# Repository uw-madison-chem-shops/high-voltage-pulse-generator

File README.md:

# High Voltage Pulse Generator 

Our adaptation of work by Nathan M. Hoffman:

>[Note: An inexpensive square waveform ion funnel driver](http://dx.doi.org/10.1063/1.4974345); Nathan M Hoffman, Bojana Bojana Opačić, and Peter T.A. Reilly; Review of Scientific Instruments, 88, 016104 (2017) 

## PCB

This PCB was designed using KiCAD version 6.
Refer to `HV-pulse-generator.pdf` for schematic.
PCB images generated with [tracespace](https://github.com/tracespace/tracespace) follow.

## Changelog

### Unprinted

### C

#### Added
- link to this repository

### B

#### Added
- initial design

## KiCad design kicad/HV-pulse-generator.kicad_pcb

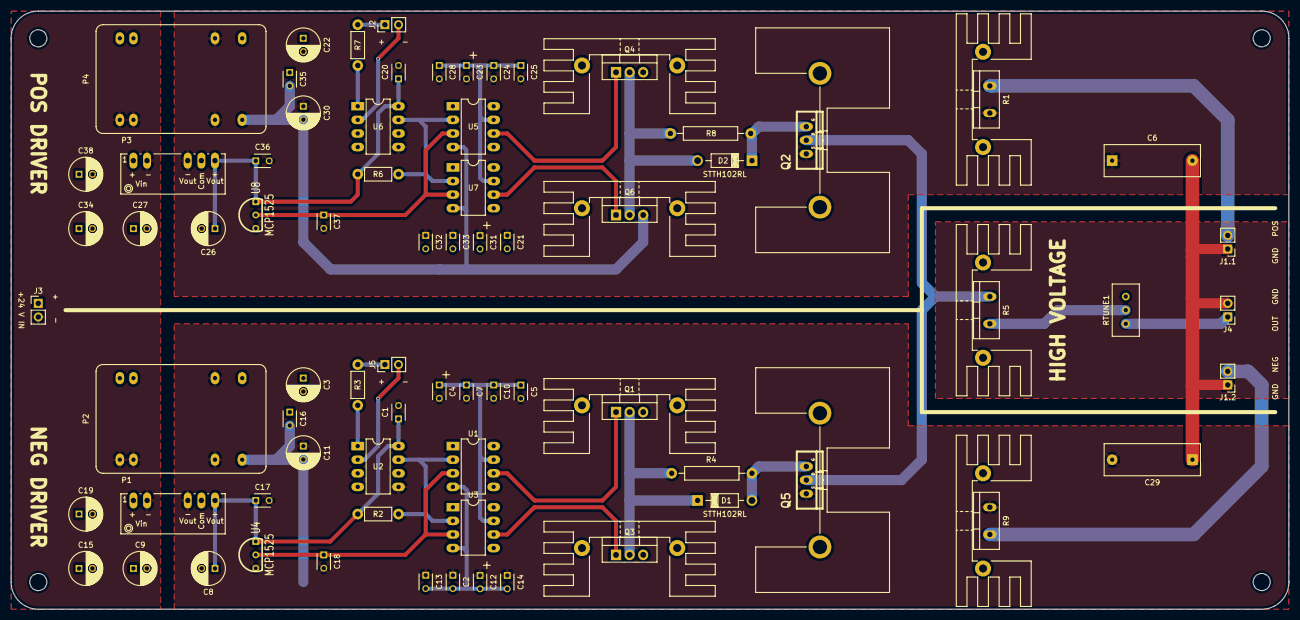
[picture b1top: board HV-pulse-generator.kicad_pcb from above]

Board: 2 copper layers, 238.8 x 111.8 mm, 74 parts (0 on the bottom side), 34 nets.

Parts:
C1, C17, C20, C36: 0.1uF; C_Disc_D3_P2.5
C2, C7, C10, C14, C16, C21, C25, C28, C33, C35: 0.01uF; C_Disc_D3_P2.5
C3, C8, C9, C11, C15, C19, C22, C26, C27, C30, C34, C38: 100uF; C_Radial_D6.3_L11.2_P2.5
C4, C12, C23, C31: 2.2uF; C_Tantalum_D3_P2.5
C5, C13, C24, C32: 1uF; C_Disc_D3_P2.5
C6, C29: 0.22uF; ECW-FA2J(10-68)4J
C18, C37: 10uF; C_Disc_D3_P2.5
D1, D2: STTH102RL; Diode_DO-41_SOD81_Horizontal_RM10
J1.1, J1.2, J3: Pin1=24V Pin2=GND; PinHeader_1x02_P2.54mm_Vertical
J2, J5: Pin1=TTL Pin2=GND; PinHeader_1x02_P2.54mm_Vertical
J4: CONN_01X02; PinHeader_1x02_P2.54mm_Vertical
P1, P3: PEM2-S24-S5-S; DCDC-Conv_CUI_PEM2_DUAL
P2, P4: JCJ0824D15
Q1, Q4: IRF9610PBF; TO-220-3_Vertical
Q2: FQP3P50; FQP3P20
Q3, Q6: IRF710PBF; TO-220-3_Vertical
Q5: FQP13N50; FQP4N20L
R1, R9: 50; Resistor_TO-220_Vertical
R2, R3, R6, R7: 365; Resistor_Horizontal_RM7mm
R4, R8: 5.1; Resistor_Horizontal_RM15mm
R5: 100; Resistor_TO-220_Vertical
RTUNE1: 200; Potentiometer_Bourns_3296W_Vertical
U1, U3, U5, U7: LM7171; DIP-8_W7.62mm_LongPads
U2, U6: ICPL2631; DIP-8_W7.62mm_LongPads
U4, U8: MCP1525; TO92-MCP1525

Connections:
+24V: C9.1, C15.1, C19.1, C27.1, C34.1, C38.1, J3.1, P1.1, P2.22, P2.23, P3.1, P4.22, P4.23
+VDC: J1.1.2, R1.2
-VDC: J1.2.2, R9.1
/Sheet5F8C1FCD/+2P5V: C18.1, U1.3, U3.3, U4.2
/Sheet5F8C1FCD/+5V: C1.1, C8.1, C17.1, P1.7, R2.2, U2.8, U4.1
/Sheet5F8C1FCD/+15V: C3.1, C4.1, C5.1, C7.1, C10.1, C16.1, P2.14, Q1.3, U1.7, U3.7
/Sheet5F8C1FCD/-15V: C2.2, C11.2, C12.2, C13.2, C14.2, C16.2, P2.11, Q3.3, U1.4, U3.4
/Sheet5F8C1FCD/COM: C1.2, C2.1, C3.2, C4.2, C5.2, C7.2, C8.2, C10.2, C11.1, C12.1, C13.1, C14.1, C17.2, C18.2, C29.2, P1.5, P2.9, P2.16, Q5.1, R9.2, U2.5, U4.3
/Sheet5F8C1FCD/GATE: D1.1, Q1.2, Q3.2, R4.2
/Sheet5F8C1FCD/TTL+: J5.1, R3.2
/Sheet5F8C1FCD/TTL-: J5.2, U2.2
/sheet5F874D32/+2P5V: C37.1, U5.3, U7.3, U8.2
/sheet5F874D32/+5V: C20.1, C26.1, C36.1, P3.7, R6.2, U6.8, U8.1
/sheet5F874D32/+15V: C22.1, C23.1, C24.1, C25.1, C28.1, C35.1, P4.14, Q4.3, U5.7, U7.7
/sheet5F874D32/-15V: C21.2, C30.2, C31.2, C32.2, C33.2, C35.2, P4.11, Q6.3, U5.4, U7.4
/sheet5F874D32/COM: C6.1, C20.2, C21.1, C22.2, C23.2, C24.2, C25.2, C26.2, C28.2, C30.1, C31.1, C32.1, C33.1, C36.2, C37.2, P3.5, P4.9, P4.16, Q2.1, R1.1, U6.5, U8.3
/sheet5F874D32/GATE: D2.2, Q4.2, Q6.2, R8.1
/sheet5F874D32/TTL+: J2.1, R7.2
/sheet5F874D32/TTL-: J2.2, U6.2
GND: C6.2, C29.1, J1.1.1, J1.2.1, J4.2
GNDPWR: C9.2, C15.2, C19.2, C27.2, C34.2, C38.2, J3.2, P1.2, P2.2, P2.3, P3.2, P4.2, P4.3
unnamed: D1.2, Q5.3, R4.1
unnamed: D2.1, Q2.3, R8.2
unnamed: J4.1, RTUNE1.3
unnamed: Q1.1, U1.6
unnamed: Q2.2, Q5.2, R5.2
unnamed: Q3.1, U3.6
unnamed: Q4.1, U5.6
unnamed: Q6.1, U7.6
unnamed: R2.1, U1.2, U2.7, U3.2
unnamed: R3.1, U2.1
unnamed: R5.1, RTUNE1.2
unnamed: R6.1, U5.2, U6.7, U7.2
unnamed: R7.1, U6.1

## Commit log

2022-05-18 kicad
